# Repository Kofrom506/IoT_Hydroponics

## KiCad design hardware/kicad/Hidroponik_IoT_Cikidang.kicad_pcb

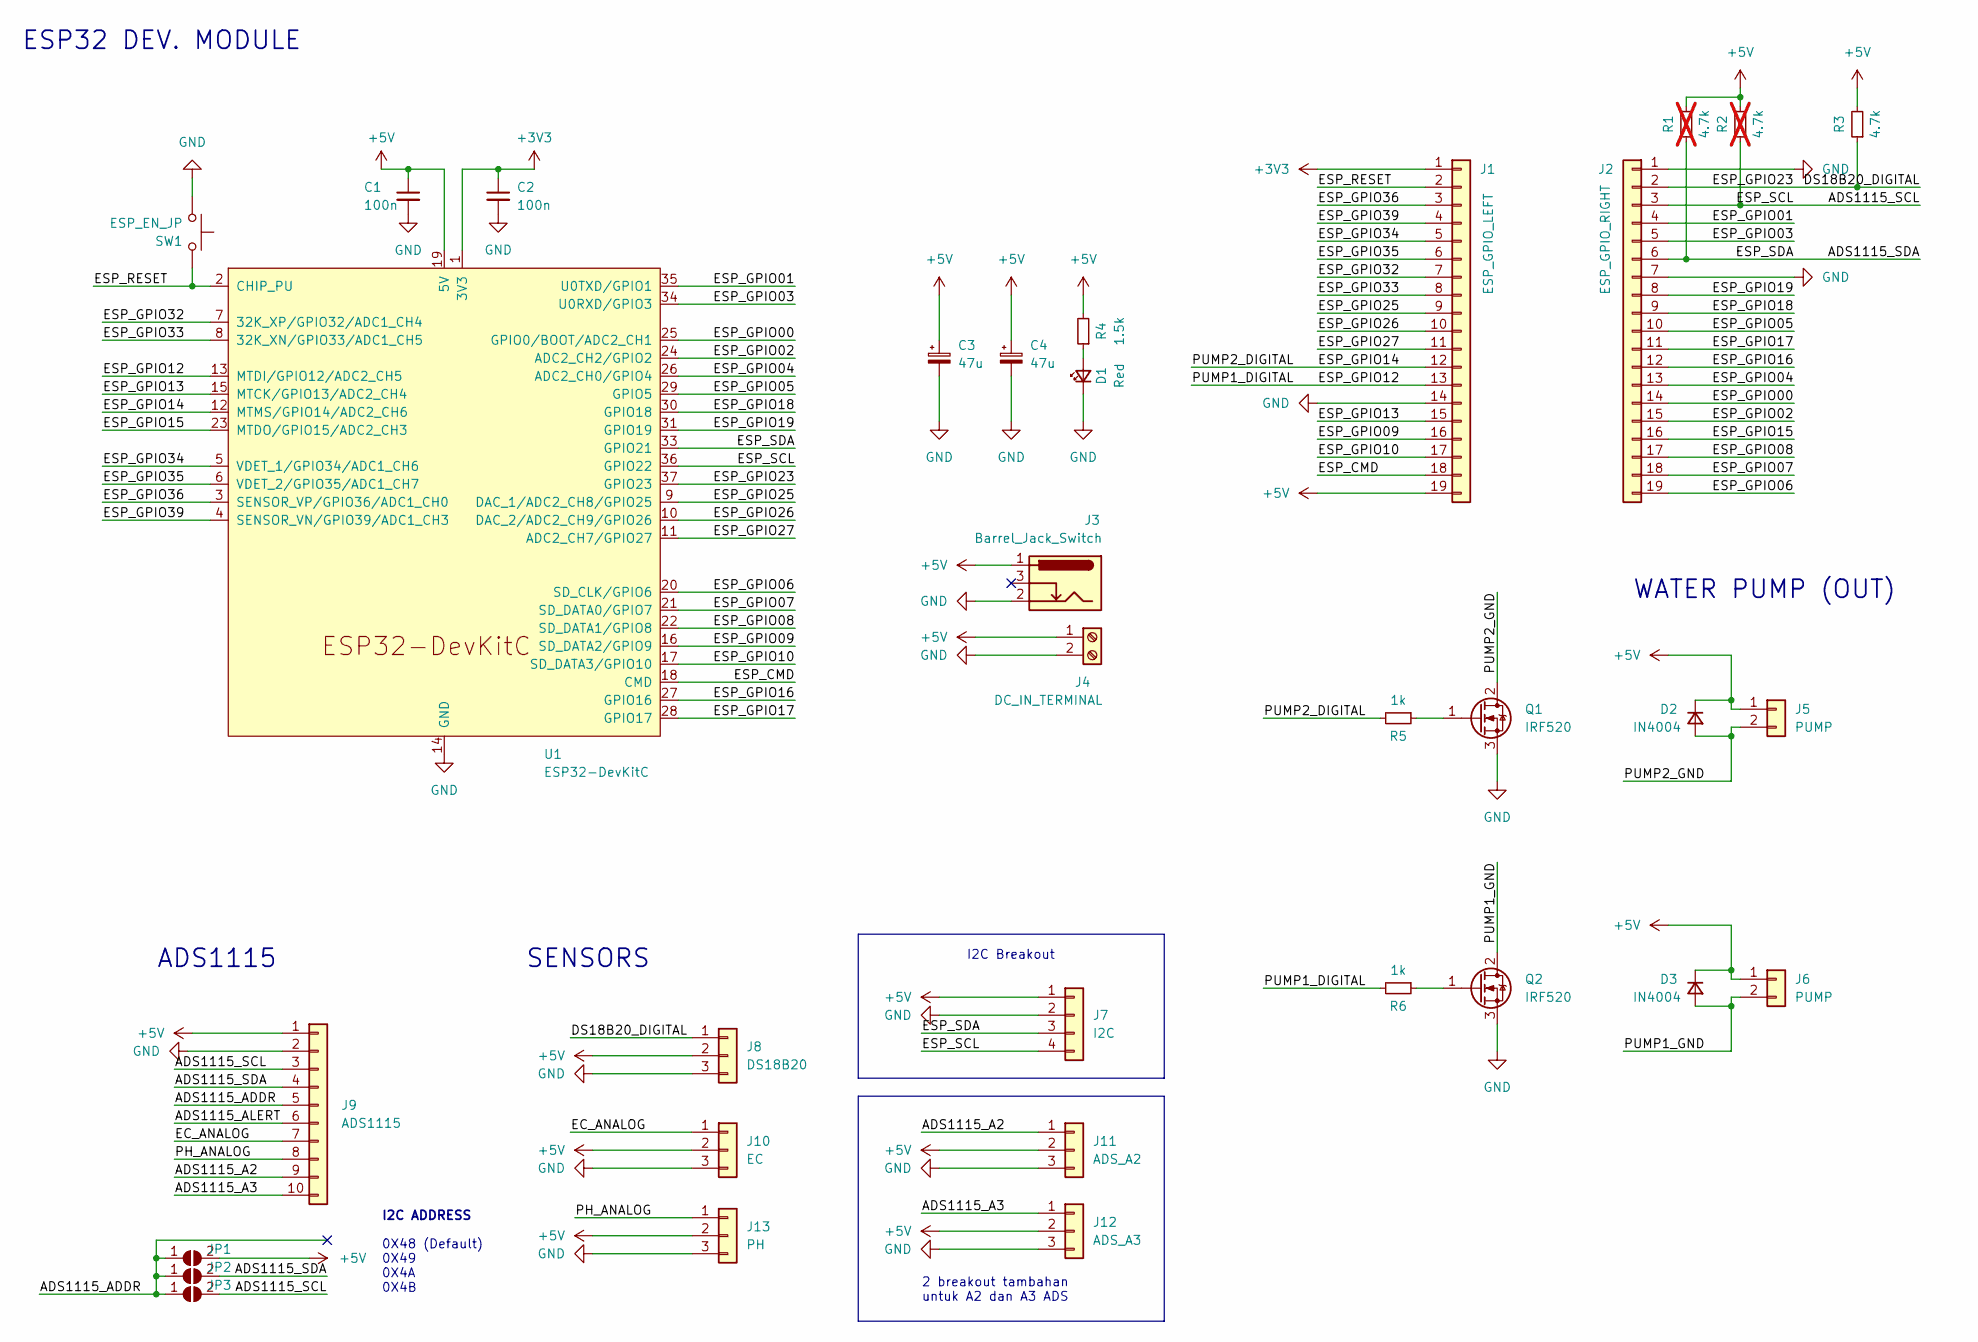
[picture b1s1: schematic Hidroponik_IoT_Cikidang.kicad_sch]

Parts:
C1, C2: 100n; C_Disc_D5.0mm_W2.5mm_P5.00mm
C3, C4: 47u; C_Radial_D5.0mm_H11.0mm_P2.00mm
D1: Red; LED_D3.0mm
D2, D3: IN4004; D_DO-34_SOD68_P7.62mm_Horizontal
J1: ESP_GPIO_LEFT; PinHeader_1x19_P2.54mm_Vertical
J2: ESP_GPIO_RIGHT; PinHeader_1x19_P2.54mm_Vertical
J3: Barrel_Jack_Switch; BarrelJack_Horizontal
J4: DC_IN_TERMINAL; TerminalBlock_Phoenix_MKDS-1,5-2-5.08_1x02_P5.08mm_Horizont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
J5, J6: PUMP; Molex_SL_171971-0002_1x02_P2.54mm_Vertical
J7: I2C; Molex_SL_171971-0004_1x04_P2.54mm_Vertical
J8: DS18B20; Molex_SL_171971-0003_1x03_P2.54mm_Vertical
J9: ADS1115; PinSocket_1x10_P2.54mm_Vertical
J10: EC; Molex_SL_171971-0003_1x03_P2.54mm_Vertical
J11: ADS_A2; Molex_SL_171971-0003_1x03_P2.54mm_Vertical
J12: ADS_A3; Molex_SL_171971-0003_1x03_P2.54mm_Vertical
J13: PH; Molex_SL_171971-0003_1x03_P2.54mm_Vertical
JP1: ADS1115_ADDR_5V; SolderJumper-2_P1.3mm_Open_RoundedPad1.0x1.5mm
JP2: ADS1115_ADDR_SDA; SolderJumper-2_P1.3mm_Open_RoundedPad1.0x1.5mm
JP3: ADS1115_ADDR_SCL; SolderJumper-2_P1.3mm_Open_RoundedPad1.0x1.5mm
Q1, Q2: IRF520; TO-220-3_Vertical
R1, R2: 4.7k; R_Axial_DIN0204_L3.6mm_D1.6mm_P7.62mm_Horizontal; not fitted
R3: 4.7k; R_Axial_DIN0204_L3.6mm_D1.6mm_P7.62mm_Horizontal
R4: 1.5k; R_Axial_DIN0204_L3.6mm_D1.6mm_P7.62mm_Horizontal
R5, R6: 1k; R_Axial_DIN0204_L3.6mm_D1.6mm_P7.62mm_Horizontal
SW1: ESP_EN_JP; Molex_SL_171971-0002_1x02_P2.54mm_Vertical
U1: ESP32-DevKitC

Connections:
+3V3: C2.1, J1.1, U1.1 (3V3)
+5V: C1.1, C3.1, C4.1, D2.1 (K), D3.1 (K), J1.19, J3.1, J4.1, J5.1, J6.1, J7.1, J8.2, J9.1, J10.2, J11.2, J12.2, J13.2, JP1.2 (B), R1.2, R2.2, R3.2, R4.2, U1.19 (5V)
/ADS1115_A2: J9.9, J11.1
/ADS1115_A3: J9.10, J12.1
/ADS1115_ADDR: J9.5, JP1.1 (A), JP2.1 (A), JP3.1 (A)
/ADS1115_ALERT: J9.6
/ADS1115_SCL: J2.3, J7.4, J9.3, JP3.2 (B), R2.1, U1.36 (GPIO22)
/ADS1115_SDA: J2.6, J7.3, J9.4, JP2.2 (B), R1.1, U1.33 (GPIO21)
/DS18B20_DIGITAL: J2.2, J8.1, R3.1, U1.37 (GPIO23)
/EC_ANALOG: J9.7, J10.1
/ESP_CMD: J1.18, U1.18 (CMD)
/ESP_GPIO00: J2.14, U1.25 (GPIO0/BOOT/ADC2_CH1)
/ESP_GPIO01: J2.4, U1.35 (U0TXD/GPIO1)
/ESP_GPIO02: J2.15, U1.24 (ADC2_CH2/GPIO2)
/ESP_GPIO03: J2.5, U1.34 (U0RXD/GPIO3)
/ESP_GPIO04: J2.13, U1.26 (ADC2_CH0/GPIO4)
/ESP_GPIO05: J2.10, U1.29 (GPIO5)
/ESP_GPIO06: J2.19, U1.20 (SD_CLK/GPIO6)
/ESP_GPIO07: J2.18, U1.21 (SD_DATA0/GPIO7)
/ESP_GPIO08: J2.17, U1.22 (SD_DATA1/GPIO8)
/ESP_GPIO09: J1.16, U1.16 (SD_DATA2/GPIO9)
/ESP_GPIO10: J1.17, U1.17 (SD_DATA3/GPIO10)
/ESP_GPIO12: J1.13, R6.2, U1.13 (MTDI/GPIO12/ADC2_CH5)
/ESP_GPIO13: J1.15, U1.15 (MTCK/GPIO13/ADC2_CH4)
/ESP_GPIO14: J1.12, R5.2, U1.12 (MTMS/GPIO14/ADC2_CH6)
/ESP_GPIO15: J2.16, U1.23 (MTDO/GPIO15/ADC2_CH3)
/ESP_GPIO16: J2.12, U1.27 (GPIO16)
/ESP_GPIO17: J2.11, U1.28 (GPIO17)
/ESP_GPIO18: J2.9, U1.30 (GPIO18)
/ESP_GPIO19: J2.8, U1.31 (GPIO19)
/ESP_GPIO25: J1.9, U1.9 (DAC_1/ADC2_CH8/GPIO25)
/ESP_GPIO26: J1.10, U1.10 (DAC_2/ADC2_CH9/GPIO26)
/ESP_GPIO27: J1.11, U1.11 (ADC2_CH7/GPIO27)
/ESP_GPIO32: J1.7, U1.7 (32K_XP/GPIO32/ADC1_CH4)
/ESP_GPIO33: J1.8, U1.8 (32K_XN/GPIO33/ADC1_CH5)
/ESP_GPIO34: J1.5, U1.5 (VDET_1/GPIO34/ADC1_CH6)
/ESP_GPIO35: J1.6, U1.6 (VDET_2/GPIO35/ADC1_CH7)
/ESP_GPIO36: J1.3, U1.3 (SENSOR_VP/GPIO36/ADC1_CH0)
/ESP_GPIO39: J1.4, U1.4 (SENSOR_VN/GPIO39/ADC1_CH3)
/ESP_RESET: J1.2, SW1.2, U1.2 (CHIP_PU)
/PH_ANALOG: J9.8, J13.1
/PUMP1_GND: D3.2 (A), J6.2, Q2.2 (D)
/PUMP2_GND: D2.2 (A), J5.2, Q1.2 (D)
GND: C1.2, C2.2, C3.2, C4.2, D1.1 (K), J1.14, J2.1, J2.7, J3.2, J4.2, J7.2, J8.3, J9.2, J10.3, J11.3, J12.3, J13.3, Q1.3 (S), Q2.3 (S), SW1.1, U1.14 (GND), U1.32 (GND), U1.38 (GND)
unnamed: D1.2 (A), R4.1
unnamed: Q1.1 (G), R5.1
unnamed: Q2.1 (G), R6.1

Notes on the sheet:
ESP32 DEV. MODULE
ADS1115
WATER PUMP (OUT)
2 breakout tambahan untuk A2 dan A3 ADS
I2C ADDRESS
I2C Breakout
0X48 (Default) 0X49 0X4A 0X4B
SENSORS

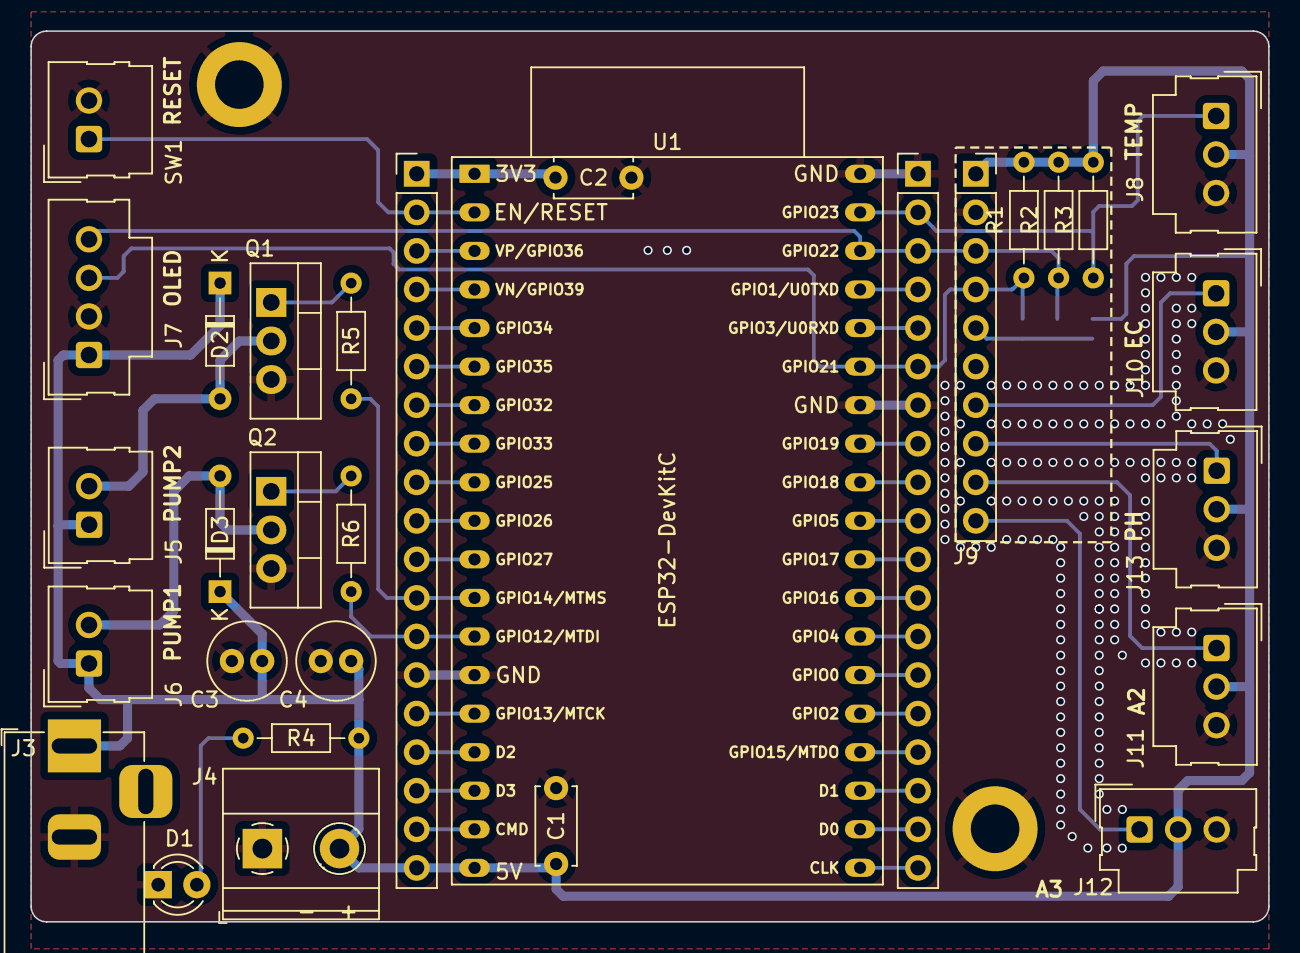
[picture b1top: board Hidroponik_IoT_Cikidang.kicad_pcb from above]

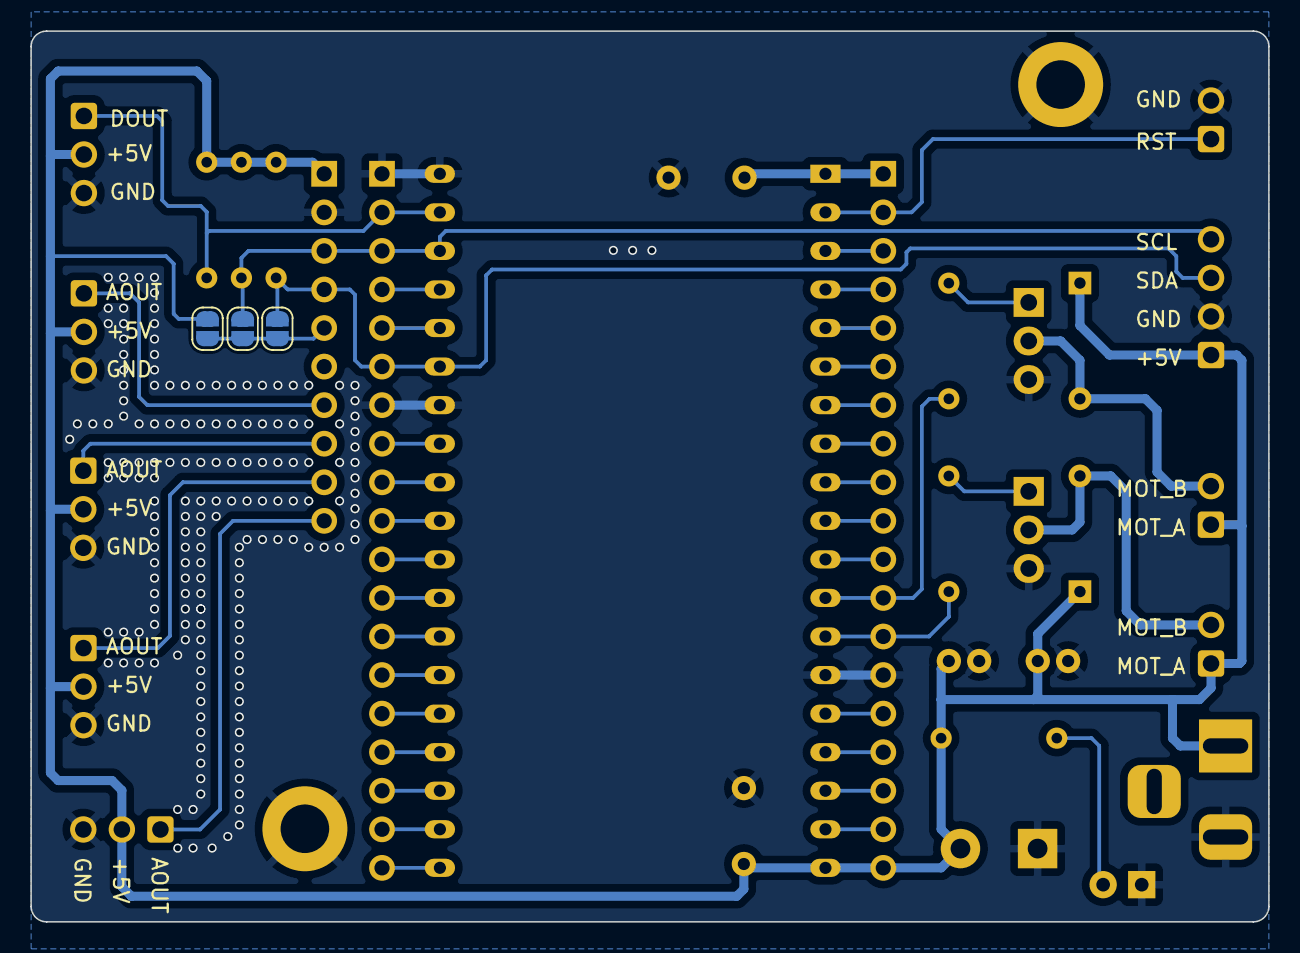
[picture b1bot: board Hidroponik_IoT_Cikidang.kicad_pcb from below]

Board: 2 copper layers, 81.5 x 58.7 mm, 33 parts (3 on the bottom side), 46 nets.

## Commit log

2023-10-23 esp32
2023-11-20 Update Schematics
2023-11-20 Rename PCB
2023-11-29 Update PCB Layout
2023-12-01 Update PCB
